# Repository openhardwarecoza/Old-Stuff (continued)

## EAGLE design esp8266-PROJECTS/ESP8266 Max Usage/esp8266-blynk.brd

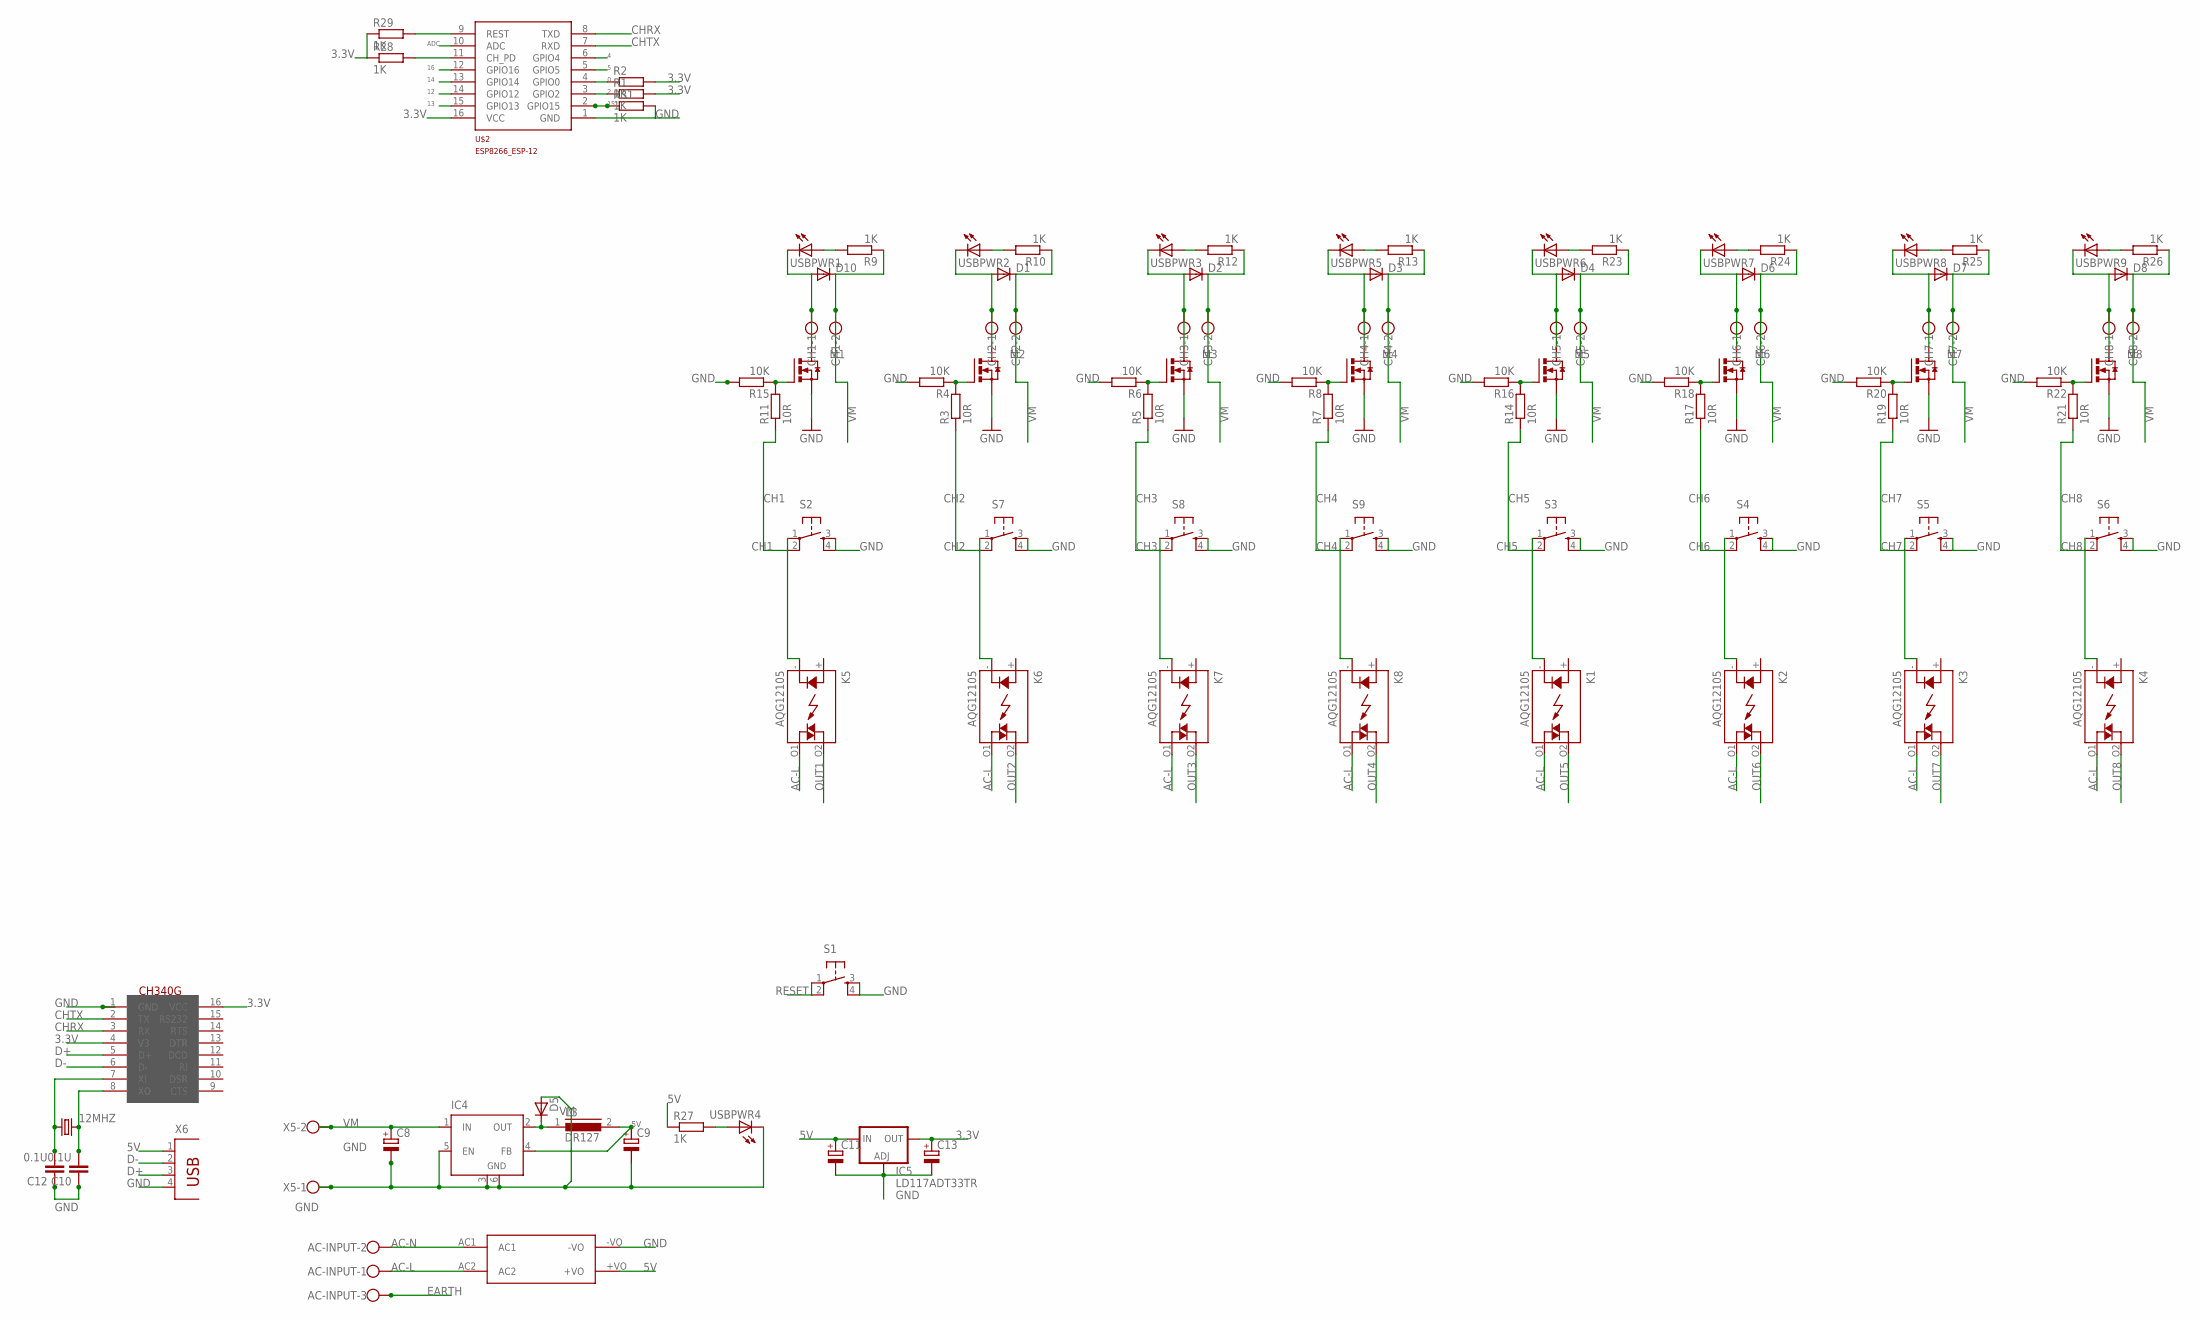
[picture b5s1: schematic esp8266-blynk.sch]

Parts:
12MHZ: CRYSTALHC49UP; HC49UP
AC-INPUT: W237-103
C8, C9: CPOL-EUE; PANASONIC_E
C10, C12: 0.1U; C1206
C11, C13: CPOL-EUC; PANASONIC_C
CH1, CH2, CH3, CH4, CH5, CH6, CH7, CH8: W237-102
D1, D2, D3, D4, D6, D7, D8, D10: DIODESMA-ALT; SMA-DIODE_ALT
D5: D-SOD-87; SOD87
IC4: LM2596S; TO263-5
IC5: LD117ADT33TR; DPACK
K1, K2, K3, K4, K5, K6, K7, K8: AQG12105; AQG
L3: DR127
M1, M2, M3, M4, M5, M6, M7, M8: IRLR024N; TO252
R1, R2, R9, R10, R12, R13, R23, R24, R25, R26, R27, R28, R29, R31: 1K; M1206
R3, R5, R7, R11, R14, R17, R19, R21: 10R; M1206
R4, R6, R8, R15, R16, R18, R20, R22: 10K; M1206
S1, S2, S3, S4, S5, S6, S7, S8, S9: TAC_SWITCHPTH; TACTILE-PTH
U$1: HLK-PM01
U$2: ESP8266_ESP-12; ESP8266-ESP12
U$4: CH340G; SOIC16
USBPWR1, USBPWR2, USBPWR3, USBPWR4, USBPWR5, USBPWR6, USBPWR7, USBPWR8, USBPWR9: LED3MM
X5: W237-102
X6: PN61729

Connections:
0: R2.1, U$2.4 (GPIO0)
2: R1.1, U$2.3 (GPIO2)
3.3V: C13.+, IC5.4 (OUT), R1.2, R2.2, R28.1, R29.1, U$2.16 (VCC), U$4.4 (V3), U$4.16 (VCC)
4: U$2.6 (GPIO4)
5: U$2.5 (GPIO5)
5V: C9.+, C11.+, IC4.4 (FB), IC5.3 (IN), L3.2, R27.1, U$1.+VO, X6.1
12: U$2.14 (GPIO12)
13: U$2.15 (GPIO13)
14: U$2.13 (GPIO14)
15: R31.1, U$2.2 (GPIO15)
16: U$2.12 (GPIO16)
AC-L: AC-INPUT.1, K1.O1 (DS2), K2.O1 (DS2), K3.O1 (DS2), K4.O1 (DS2), K5.O1 (DS2), K6.O1 (DS2), K7.O1 (DS2), K8.O1 (DS2), U$1.AC2
AC-N: AC-INPUT.2, U$1.AC1
ADC: U$2.10 (ADC)
CH1: K5.- (K), R11.1, S2.1, S2.2
CH2: K6.- (K), R3.1, S7.1, S7.2
CH3: K7.- (K), R5.1, S8.1, S8.2
CH4: K8.- (K), R7.1, S9.1, S9.2
CH5: K1.- (K), R14.1, S3.1, S3.2
CH6: K2.- (K), R17.1, S4.1, S4.2
CH7: K3.- (K), R19.1, S5.1, S5.2
CH8: K4.- (K), R21.1, S6.1, S6.2
CHRX: U$2.8 (TXD), U$4.3 (RX)
CHTX: U$2.7 (RXD), U$4.2 (TX)
D+: U$4.5 (D+), X6.3
D-: U$4.6 (D-), X6.2
EARTH: AC-INPUT.3
GND: C8.-, C9.-, C10.1, C11.-, C12.1, C13.-, D5.2 (A), IC4.3 (GND), IC4.5 (EN), IC4.6 (GND), IC5.1 (ADJ), M1.2 (S), M2.2 (S), M3.2 (S), M4.2 (S), M5.2 (S), M6.2 (S), M7.2 (S), M8.2 (S), R4.2, R6.2, R8.2, R15.2, R16.2, R18.2, R20.2, R22.2, R31.2, S1.3, S1.4, S2.3, S2.4, S3.3, S3.4, S4.3, S4.4, S5.3, S5.4, S6.3, S6.4, S7.3, S7.4, S8.3, S8.4, S9.3, S9.4, U$1.-VO, U$2.1 (GND), U$4.1 (GND), USBPWR4.K (C), X5.1, X6.4
unnamed: M2.1 (G), R3.2, R4.1
unnamed: M3.1 (G), R5.2, R6.1
unnamed: M4.1 (G), R7.2, R8.1
unnamed: R9.2, USBPWR1.A
unnamed: R10.2, USBPWR2.A
unnamed: R12.2, USBPWR3.A
unnamed: R13.2, USBPWR5.A
unnamed: D5.1 (C), IC4.2 (OUT), L3.1
unnamed: R27.2, USBPWR4.A
unnamed: 12MHZ.1, C12.2, U$4.7 (XI)
unnamed: 12MHZ.2, C10.2, U$4.8 (XO)
unnamed: M5.1 (G), R14.2, R16.1
unnamed: R28.2, U$2.11 (CH_PD)
unnamed: M6.1 (G), R17.2, R18.1
unnamed: M7.1 (G), R19.2, R20.1
unnamed: M8.1 (G), R21.2, R22.1
unnamed: R23.2, USBPWR6.A
unnamed: R24.2, USBPWR7.A
unnamed: R25.2, USBPWR8.A
unnamed: R26.2, USBPWR9.A
unnamed: M1.1 (G), R11.2, R15.1
OUT1: CH1.1, D10.A, K5.O2 (DS1), M1.3 (D), USBPWR1.K (C)
OUT2: CH2.1, D1.A, K6.O2 (DS1), M2.3 (D), USBPWR2.K (C)
OUT3: CH3.1, D2.A, K7.O2 (DS1), M3.3 (D), USBPWR3.K (C)
OUT4: CH4.1, D3.A, K8.O2 (DS1), M4.3 (D), USBPWR5.K (C)
OUT5: CH5.1, D4.A, K1.O2 (DS1), M5.3 (D), USBPWR6.K (C)
OUT6: CH6.1, D6.A, K2.O2 (DS1), M6.3 (D), USBPWR7.K (C)
OUT7: CH7.1, D7.A, K3.O2 (DS1), M7.3 (D), USBPWR8.K (C)
OUT8: CH8.1, D8.A, K4.O2 (DS1), M8.3 (D), USBPWR9.K (C)
RESET: R29.2, S1.1, S1.2, U$2.9 (REST)
VM: C8.+, CH1.2, CH2.2, CH3.2, CH4.2, CH5.2, CH6.2, CH7.2, CH8.2, D1.C, D2.C, D3.C, D4.C, D6.C, D7.C, D8.C, D10.C, IC4.1 (IN), R9.1, R10.1, R12.1, R13.1, R23.1, R24.1, R25.1, R26.1, X5.2

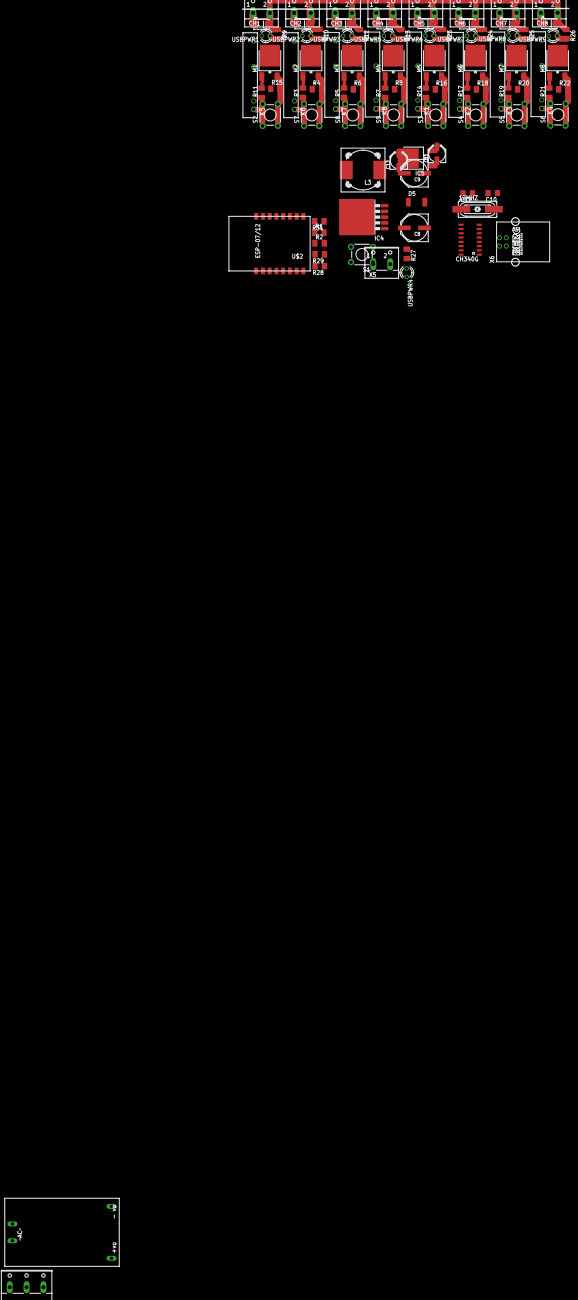
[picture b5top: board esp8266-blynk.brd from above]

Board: 2 copper layers, 97 parts (0 on the bottom side), 51 nets.

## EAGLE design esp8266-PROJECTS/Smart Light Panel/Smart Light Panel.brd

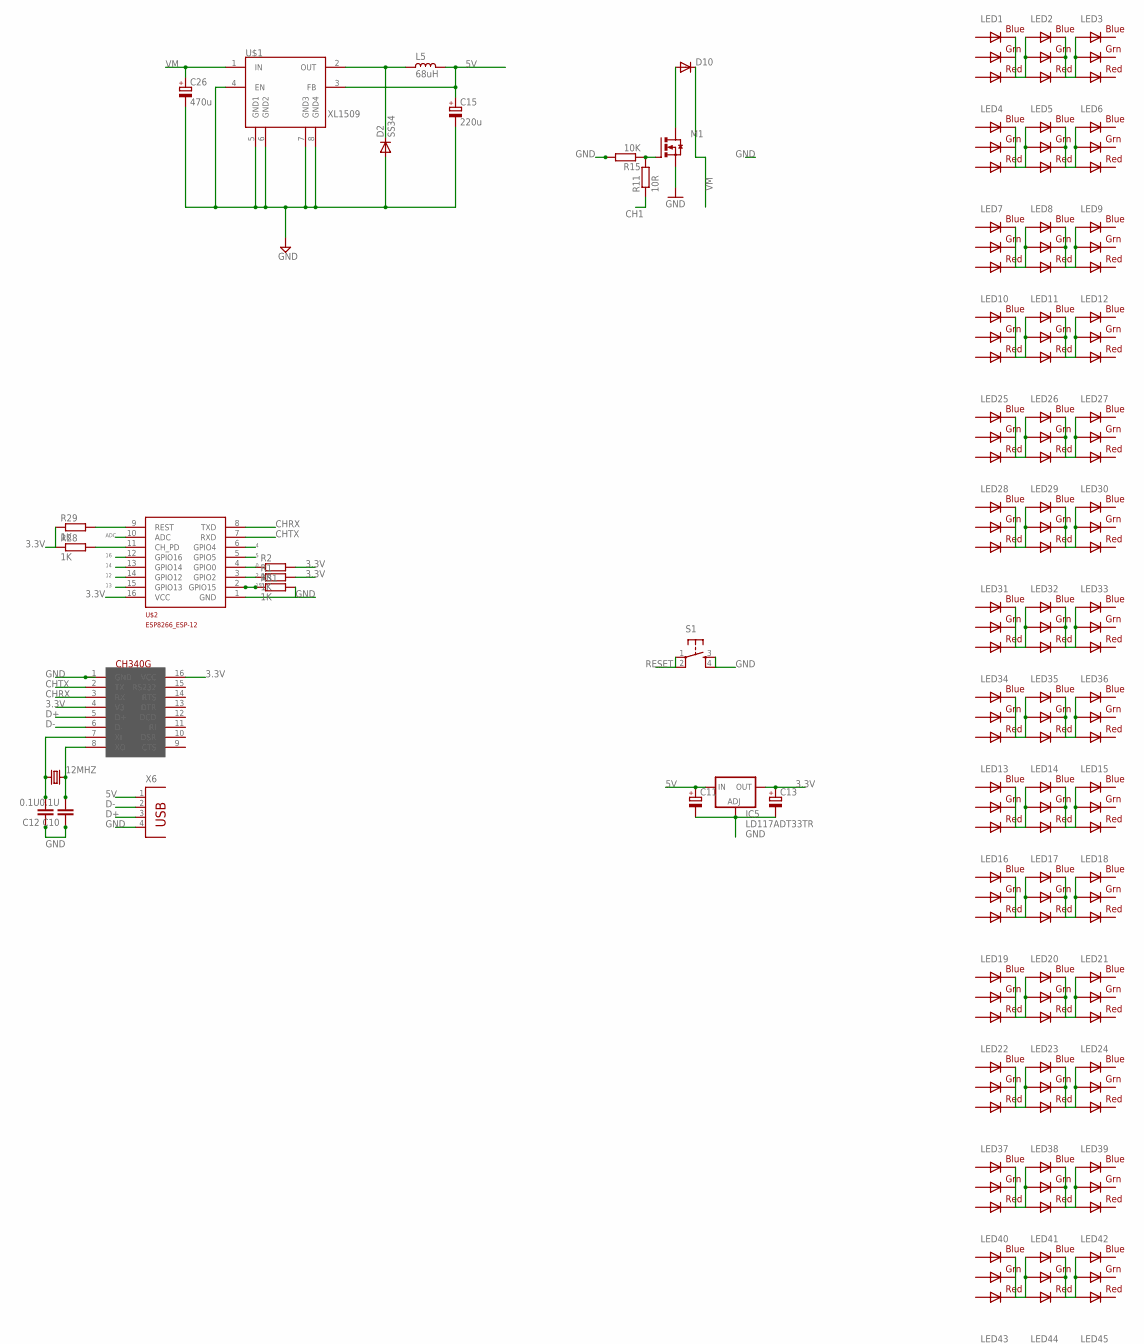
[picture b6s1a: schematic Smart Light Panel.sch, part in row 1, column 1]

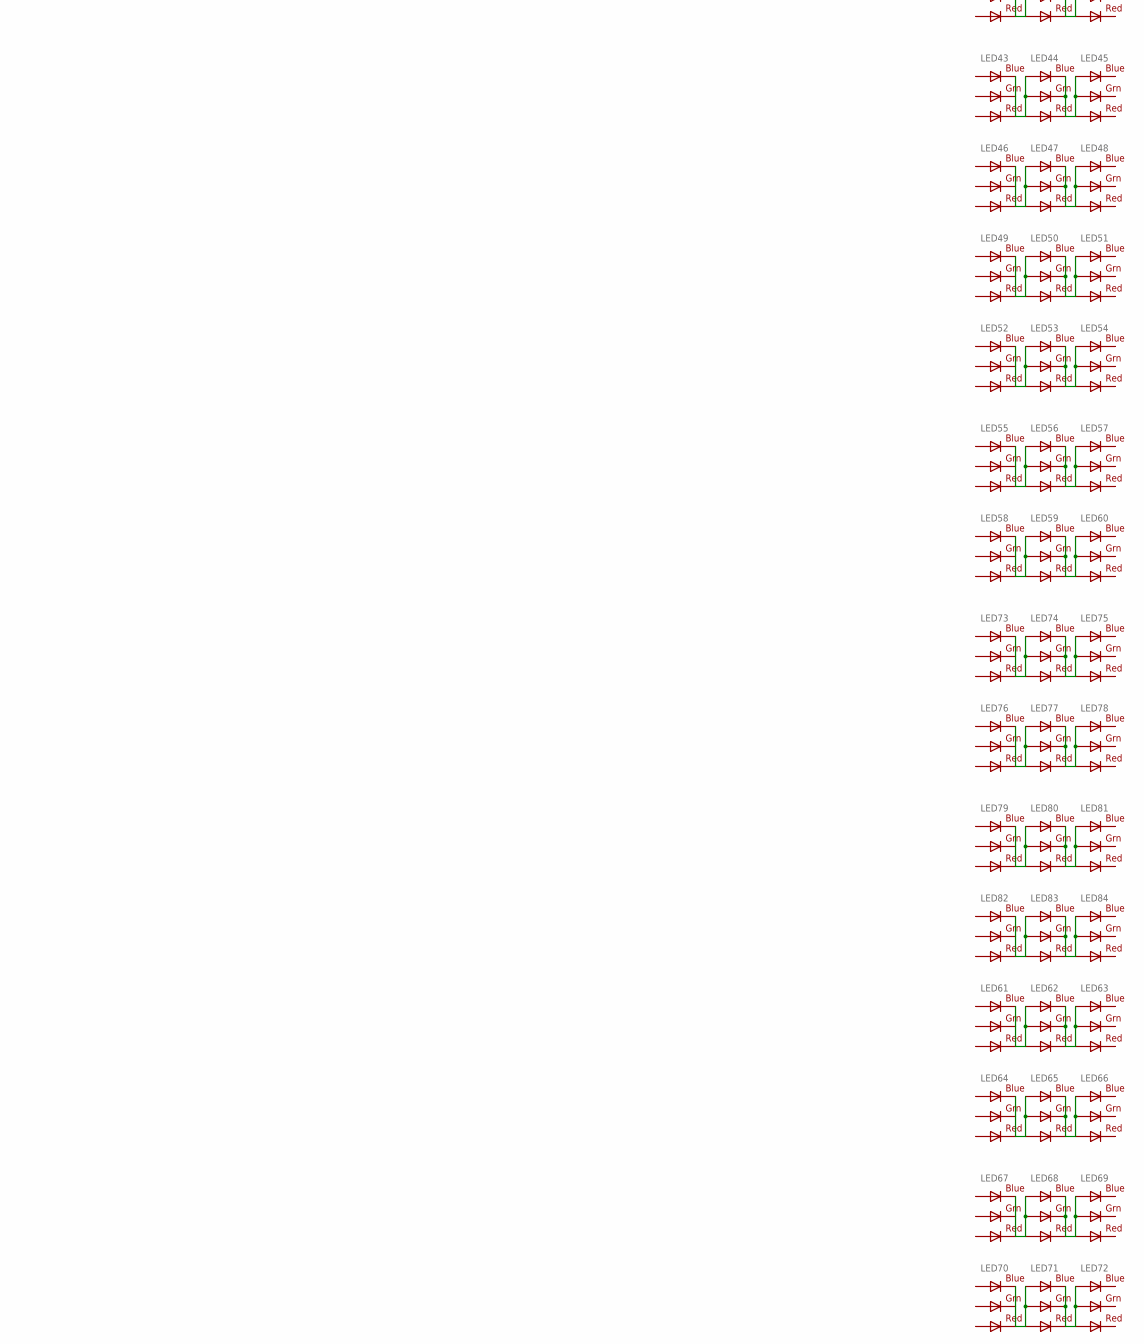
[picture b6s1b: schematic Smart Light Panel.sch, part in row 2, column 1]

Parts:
12MHZ: CRYSTALHC49UP; HC49UP
C10, C12: 0.1U; C1206
C11, C13: CPOL-EUC; PANASONIC_C
C15: 220u; E2,5-7
C26: 470u; E2,5-7
D2: SS34; DO-214AC
D10: DIODESMA-ALT; SMA-DIODE_ALT
IC5: LD117ADT33TR; DPACK
L5: 68uH; CD75
LED1, LED2, LED3, LED4, LED5, LED6, LED7, LED8, LED9, LED10, LED11, LED12, LED13, LED14, LED15, LED16, LED17, LED18, LED19, LED20, LED21, LED22, LED23, LED24, LED25, LED26, LED27, LED28, LED29, LED30, LED31, LED32, LED33, LED34, LED35, LED36, LED37, LED38, LED39, LED40, LED41, LED42, LED43, LED44, LED45, LED46, LED47, LED48, LED49, LED50, LED51, LED52, LED53, LED54, LED55, LED56, LED57, LED58, LED59, LED60, LED61, LED62, LED63, LED64, LED65, LED66, LED67, LED68, LED69, LED70, LED71, LED72, LED73, LED74, LED75, LED76, LED77, LED78, LED79, LED80, LED81, LED82, LED83, LED84: RGBLED5050
M1: IRLR024N; TO252
R1, R2, R28, R29, R31: 1K; M1206
R11: 10R; M1206
R15: 10K; M1206
S1: TAC_SWITCHPTH; TACTILE-PTH
U$1: XL1509; SO08
U$2: ESP8266_ESP-12; ESP8266-ESP12
U$4: CH340G; SOIC16
X6: PN61729

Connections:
0: R2.1, U$2.4 (GPIO0)
2: R1.1, U$2.3 (GPIO2)
3.3V: C13.+, IC5.4 (OUT), R1.2, R2.2, R28.1, R29.1, U$2.16 (VCC), U$4.4 (V3), U$4.16 (VCC)
4: U$2.6 (GPIO4)
5: U$2.5 (GPIO5)
5V: C11.+, C15.+, IC5.3 (IN), L5.1, U$1.3 (FB), X6.1
12: U$2.14 (GPIO12)
13: U$2.15 (GPIO13)
14: U$2.13 (GPIO14)
15: R31.1, U$2.2 (GPIO15)
16: U$2.12 (GPIO16)
ADC: U$2.10 (ADC)
CH1: R11.1
CHRX: U$2.8 (TXD), U$4.3 (RX)
CHTX: U$2.7 (RXD), U$4.2 (TX)
D+: U$4.5 (D+), X6.3
D-: U$4.6 (D-), X6.2
GND: C10.1, C11.-, C12.1, C13.-, C15.-, C26.-, D2.2 (A), IC5.1 (ADJ), M1.2 (S), R15.2, R31.2, S1.3, S1.4, U$1.4 (EN), U$1.5 (GND1), U$1.6 (GND2), U$1.7 (GND3), U$1.8 (GND4), U$2.1 (GND), U$4.1 (GND), X6.4
MOSFET: D10.A, M1.3 (D)
unnamed: LED1.4 (BLUE_C), LED1.5 (RED_C), LED1.6 (GREEN_C), LED2.1 (GREEN_A), LED2.2 (RED_A), LED2.3 (BLUE_A)
unnamed: LED2.4 (BLUE_C), LED2.5 (RED_C), LED2.6 (GREEN_C), LED3.1 (GREEN_A), LED3.2 (RED_A), LED3.3 (BLUE_A)
unnamed: LED4.4 (BLUE_C), LED4.5 (RED_C), LED4.6 (GREEN_C), LED5.1 (GREEN_A), LED5.2 (RED_A), LED5.3 (BLUE_A)
unnamed: LED5.4 (BLUE_C), LED5.5 (RED_C), LED5.6 (GREEN_C), LED6.1 (GREEN_A), LED6.2 (RED_A), LED6.3 (BLUE_A)
unnamed: LED7.4 (BLUE_C), LED7.5 (RED_C), LED7.6 (GREEN_C), LED8.1 (GREEN_A), LED8.2 (RED_A), LED8.3 (BLUE_A)
unnamed: 12MHZ.1, C12.2, U$4.7 (XI)
unnamed: 12MHZ.2, C10.2, U$4.8 (XO)
unnamed: LED8.4 (BLUE_C), LED8.5 (RED_C), LED8.6 (GREEN_C), LED9.1 (GREEN_A), LED9.2 (RED_A), LED9.3 (BLUE_A)
unnamed: LED10.4 (BLUE_C), LED10.5 (RED_C), LED10.6 (GREEN_C), LED11.1 (GREEN_A), LED11.2 (RED_A), LED11.3 (BLUE_A)
unnamed: LED11.4 (BLUE_C), LED11.5 (RED_C), LED11.6 (GREEN_C), LED12.1 (GREEN_A), LED12.2 (RED_A), LED12.3 (BLUE_A)
unnamed: R28.2, U$2.11 (CH_PD)
unnamed: LED13.4 (BLUE_C), LED13.5 (RED_C), LED13.6 (GREEN_C), LED14.1 (GREEN_A), LED14.2 (RED_A), LED14.3 (BLUE_A)
unnamed: LED14.4 (BLUE_C), LED14.5 (RED_C), LED14.6 (GREEN_C), LED15.1 (GREEN_A), LED15.2 (RED_A), LED15.3 (BLUE_A)
unnamed: LED16.4 (BLUE_C), LED16.5 (RED_C), LED16.6 (GREEN_C), LED17.1 (GREEN_A), LED17.2 (RED_A), LED17.3 (BLUE_A)
unnamed: LED17.4 (BLUE_C), LED17.5 (RED_C), LED17.6 (GREEN_C), LED18.1 (GREEN_A), LED18.2 (RED_A), LED18.3 (BLUE_A)
unnamed: LED19.4 (BLUE_C), LED19.5 (RED_C), LED19.6 (GREEN_C), LED20.1 (GREEN_A), LED20.2 (RED_A), LED20.3 (BLUE_A)
unnamed: LED20.4 (BLUE_C), LED20.5 (RED_C), LED20.6 (GREEN_C), LED21.1 (GREEN_A), LED21.2 (RED_A), LED21.3 (BLUE_A)
unnamed: LED22.4 (BLUE_C), LED22.5 (RED_C), LED22.6 (GREEN_C), LED23.1 (GREEN_A), LED23.2 (RED_A), LED23.3 (BLUE_A)
unnamed: LED23.4 (BLUE_C), LED23.5 (RED_C), LED23.6 (GREEN_C), LED24.1 (GREEN_A), LED24.2 (RED_A), LED24.3 (BLUE_A)
unnamed: LED25.4 (BLUE_C), LED25.5 (RED_C), LED25.6 (GREEN_C), LED26.1 (GREEN_A), LED26.2 (RED_A), LED26.3 (BLUE_A)
unnamed: LED26.4 (BLUE_C), LED26.5 (RED_C), LED26.6 (GREEN_C), LED27.1 (GREEN_A), LED27.2 (RED_A), LED27.3 (BLUE_A)
unnamed: LED28.4 (BLUE_C), LED28.5 (RED_C), LED28.6 (GREEN_C), LED29.1 (GREEN_A), LED29.2 (RED_A), LED29.3 (BLUE_A)
unnamed: LED29.4 (BLUE_C), LED29.5 (RED_C), LED29.6 (GREEN_C), LED30.1 (GREEN_A), LED30.2 (RED_A), LED30.3 (BLUE_A)
unnamed: LED31.4 (BLUE_C), LED31.5 (RED_C), LED31.6 (GREEN_C), LED32.1 (GREEN_A), LED32.2 (RED_A), LED32.3 (BLUE_A)
unnamed: LED32.4 (BLUE_C), LED32.5 (RED_C), LED32.6 (GREEN_C), LED33.1 (GREEN_A), LED33.2 (RED_A), LED33.3 (BLUE_A)
unnamed: LED34.4 (BLUE_C), LED34.5 (RED_C), LED34.6 (GREEN_C), LED35.1 (GREEN_A), LED35.2 (RED_A), LED35.3 (BLUE_A)
unnamed: LED35.4 (BLUE_C), LED35.5 (RED_C), LED35.6 (GREEN_C), LED36.1 (GREEN_A), LED36.2 (RED_A), LED36.3 (BLUE_A)
unnamed: LED37.4 (BLUE_C), LED37.5 (RED_C), LED37.6 (GREEN_C), LED38.1 (GREEN_A), LED38.2 (RED_A), LED38.3 (BLUE_A)
unnamed: LED38.4 (BLUE_C), LED38.5 (RED_C), LED38.6 (GREEN_C), LED39.1 (GREEN_A), LED39.2 (RED_A), LED39.3 (BLUE_A)
unnamed: LED40.4 (BLUE_C), LED40.5 (RED_C), LED40.6 (GREEN_C), LED41.1 (GREEN_A), LED41.2 (RED_A), LED41.3 (BLUE_A)
unnamed: LED41.4 (BLUE_C), LED41.5 (RED_C), LED41.6 (GREEN_C), LED42.1 (GREEN_A), LED42.2 (RED_A), LED42.3 (BLUE_A)
unnamed: LED43.4 (BLUE_C), LED43.5 (RED_C), LED43.6 (GREEN_C), LED44.1 (GREEN_A), LED44.2 (RED_A), LED44.3 (BLUE_A)
unnamed: LED44.4 (BLUE_C), LED44.5 (RED_C), LED44.6 (GREEN_C), LED45.1 (GREEN_A), LED45.2 (RED_A), LED45.3 (BLUE_A)
unnamed: LED46.4 (BLUE_C), LED46.5 (RED_C), LED46.6 (GREEN_C), LED47.1 (GREEN_A), LED47.2 (RED_A), LED47.3 (BLUE_A)
unnamed: LED47.4 (BLUE_C), LED47.5 (RED_C), LED47.6 (GREEN_C), LED48.1 (GREEN_A), LED48.2 (RED_A), LED48.3 (BLUE_A)
unnamed: LED49.4 (BLUE_C), LED49.5 (RED_C), LED49.6 (GREEN_C), LED50.1 (GREEN_A), LED50.2 (RED_A), LED50.3 (BLUE_A)
unnamed: LED50.4 (BLUE_C), LED50.5 (RED_C), LED50.6 (GREEN_C), LED51.1 (GREEN_A), LED51.2 (RED_A), LED51.3 (BLUE_A)
unnamed: LED52.4 (BLUE_C), LED52.5 (RED_C), LED52.6 (GREEN_C), LED53.1 (GREEN_A), LED53.2 (RED_A), LED53.3 (BLUE_A)
unnamed: LED53.4 (BLUE_C), LED53.5 (RED_C), LED53.6 (GREEN_C), LED54.1 (GREEN_A), LED54.2 (RED_A), LED54.3 (BLUE_A)
unnamed: LED55.4 (BLUE_C), LED55.5 (RED_C), LED55.6 (GREEN_C), LED56.1 (GREEN_A), LED56.2 (RED_A), LED56.3 (BLUE_A)
unnamed: LED56.4 (BLUE_C), LED56.5 (RED_C), LED56.6 (GREEN_C), LED57.1 (GREEN_A), LED57.2 (RED_A), LED57.3 (BLUE_A)
unnamed: LED58.4 (BLUE_C), LED58.5 (RED_C), LED58.6 (GREEN_C), LED59.1 (GREEN_A), LED59.2 (RED_A), LED59.3 (BLUE_A)
unnamed: LED59.4 (BLUE_C), LED59.5 (RED_C), LED59.6 (GREEN_C), LED60.1 (GREEN_A), LED60.2 (RED_A), LED60.3 (BLUE_A)
unnamed: M1.1 (G), R11.2, R15.1
unnamed: LED61.4 (BLUE_C), LED61.5 (RED_C), LED61.6 (GREEN_C), LED62.1 (GREEN_A), LED62.2 (RED_A), LED62.3 (BLUE_A)
unnamed: LED62.4 (BLUE_C), LED62.5 (RED_C), LED62.6 (GREEN_C), LED63.1 (GREEN_A), LED63.2 (RED_A), LED63.3 (BLUE_A)
unnamed: LED64.4 (BLUE_C), LED64.5 (RED_C), LED64.6 (GREEN_C), LED65.1 (GREEN_A), LED65.2 (RED_A), LED65.3 (BLUE_A)
unnamed: LED65.4 (BLUE_C), LED65.5 (RED_C), LED65.6 (GREEN_C), LED66.1 (GREEN_A), LED66.2 (RED_A), LED66.3 (BLUE_A)
unnamed: LED67.4 (BLUE_C), LED67.5 (RED_C), LED67.6 (GREEN_C), LED68.1 (GREEN_A), LED68.2 (RED_A), LED68.3 (BLUE_A)
unnamed: LED68.4 (BLUE_C), LED68.5 (RED_C), LED68.6 (GREEN_C), LED69.1 (GREEN_A), LED69.2 (RED_A), LED69.3 (BLUE_A)
unnamed: LED70.4 (BLUE_C), LED70.5 (RED_C), LED70.6 (GREEN_C), LED71.1 (GREEN_A), LED71.2 (RED_A), LED71.3 (BLUE_A)
unnamed: LED71.4 (BLUE_C), LED71.5 (RED_C), LED71.6 (GREEN_C), LED72.1 (GREEN_A), LED72.2 (RED_A), LED72.3 (BLUE_A)
unnamed: LED73.4 (BLUE_C), LED73.5 (RED_C), LED73.6 (GREEN_C), LED74.1 (GREEN_A), LED74.2 (RED_A), LED74.3 (BLUE_A)
unnamed: LED74.4 (BLUE_C), LED74.5 (RED_C), LED74.6 (GREEN_C), LED75.1 (GREEN_A), LED75.2 (RED_A), LED75.3 (BLUE_A)
unnamed: LED76.4 (BLUE_C), LED76.5 (RED_C), LED76.6 (GREEN_C), LED77.1 (GREEN_A), LED77.2 (RED_A), LED77.3 (BLUE_A)
unnamed: LED77.4 (BLUE_C), LED77.5 (RED_C), LED77.6 (GREEN_C), LED78.1 (GREEN_A), LED78.2 (RED_A), LED78.3 (BLUE_A)
unnamed: LED79.4 (BLUE_C), LED79.5 (RED_C), LED79.6 (GREEN_C), LED80.1 (GREEN_A), LED80.2 (RED_A), LED80.3 (BLUE_A)
unnamed: LED80.4 (BLUE_C), LED80.5 (RED_C), LED80.6 (GREEN_C), LED81.1 (GREEN_A), LED81.2 (RED_A), LED81.3 (BLUE_A)
unnamed: LED82.4 (BLUE_C), LED82.5 (RED_C), LED82.6 (GREEN_C), LED83.1 (GREEN_A), LED83.2 (RED_A), LED83.3 (BLUE_A)
unnamed: LED83.4 (BLUE_C), LED83.5 (RED_C), LED83.6 (GREEN_C), LED84.1 (GREEN_A), LED84.2 (RED_A), LED84.3 (BLUE_A)
unnamed: D2.1 (C), L5.2, U$1.2 (OUT)
RESET: R29.2, S1.1, S1.2, U$2.9 (REST)
VM: C26.+, D10.C, U$1.1 (IN)

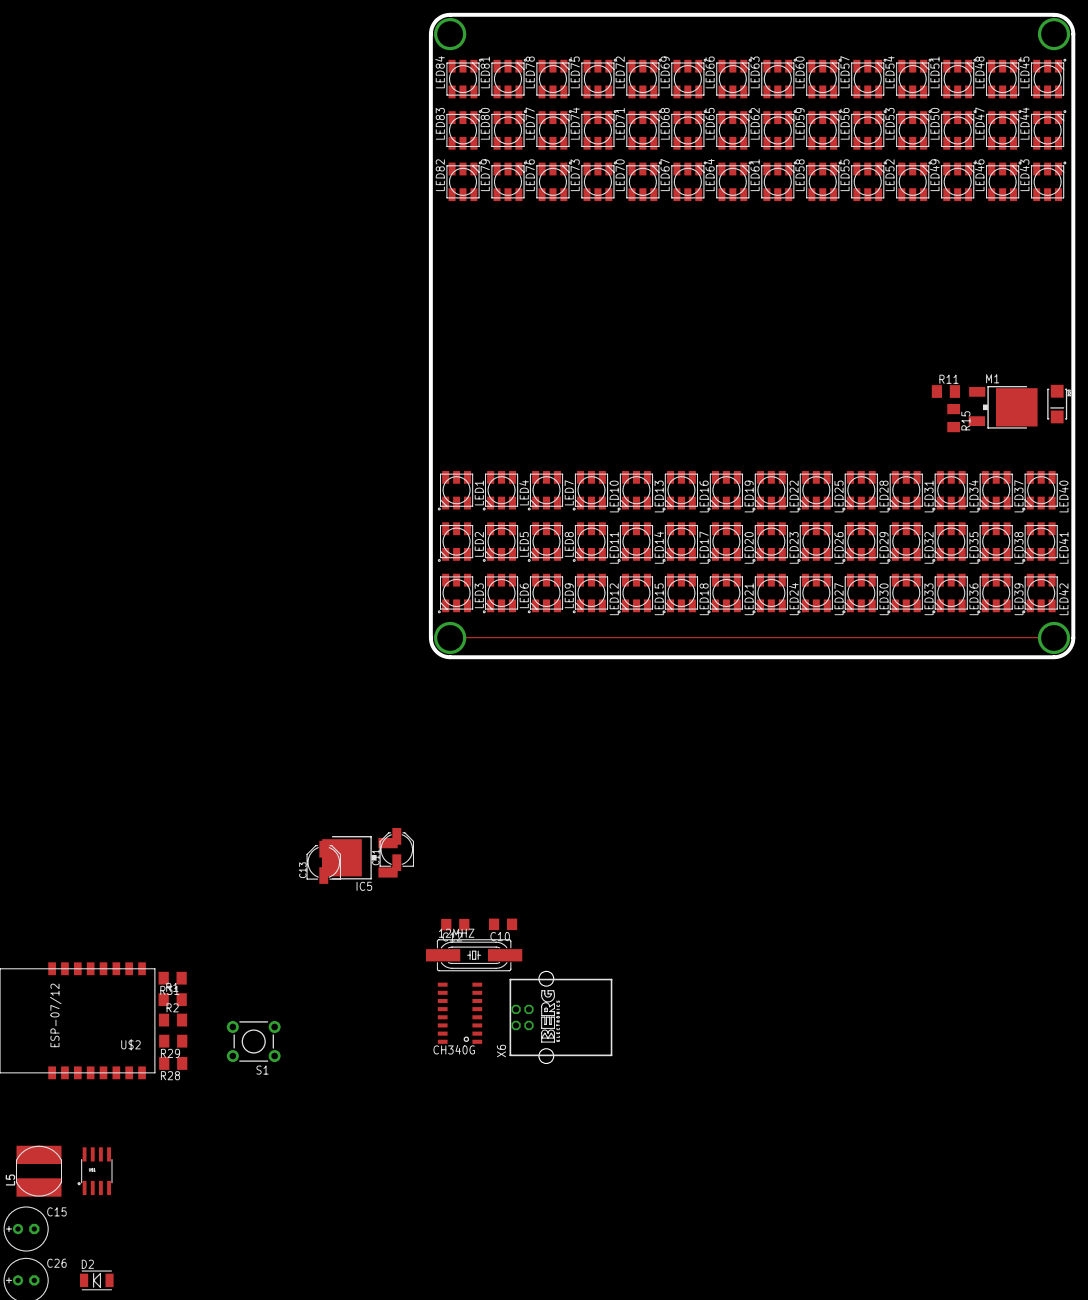
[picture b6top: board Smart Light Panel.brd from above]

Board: 2 copper layers, 100.0 x 100.0 mm, 108 parts (0 on the bottom side), 74 nets.
